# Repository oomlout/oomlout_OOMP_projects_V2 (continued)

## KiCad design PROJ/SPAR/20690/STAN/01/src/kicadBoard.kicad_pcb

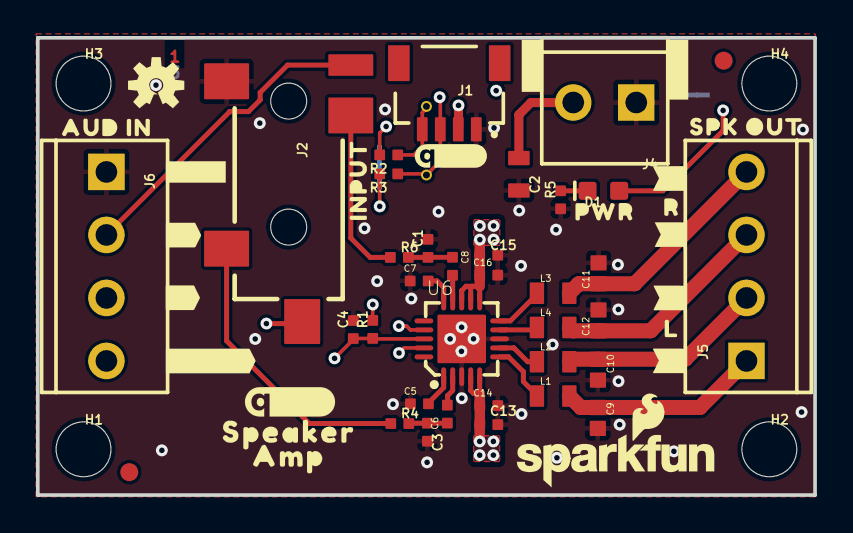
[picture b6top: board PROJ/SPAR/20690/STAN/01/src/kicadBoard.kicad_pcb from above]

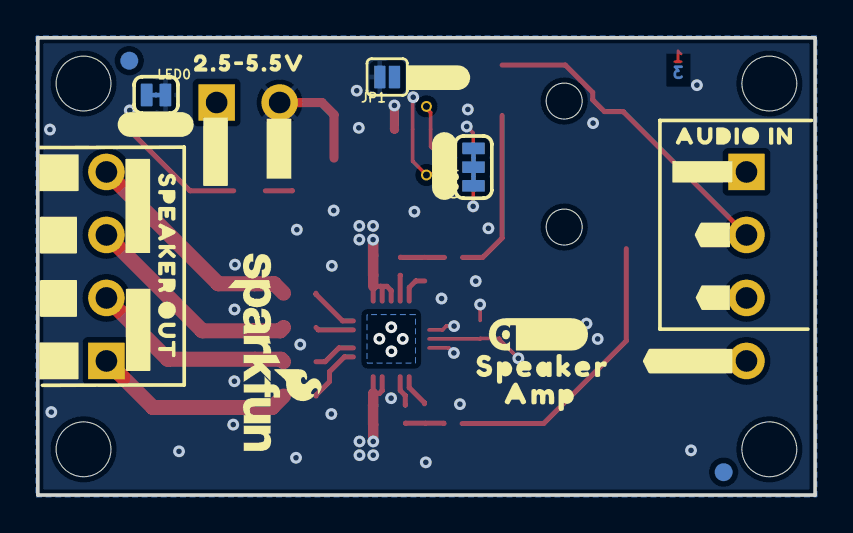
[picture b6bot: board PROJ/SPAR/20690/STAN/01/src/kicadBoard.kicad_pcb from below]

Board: 4 copper layers, 43.2 x 25.4 mm, 92 parts (27 on the bottom side), 28 nets.

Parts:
C1, C3: 47nF; 0402-TIGHT
C2: 10uF; 0805
C4, C14, C16: 0.1uF; 0402-TIGHT
C5, C6, C7, C8, C13, C15: 1.0uF; 0402-TIGHT
C9, C10, C11, C12: 1nF; 0402
D1: RED; LED-0603
FD1, FD2, FD3, FD4: FIDUCIAL1X2; FIDUCIAL-1X2
FRAME2: FRAME-LETTER; CREATIVE_COMMONS
H1, H2, H3, H4: STAND-OFFTIGHT; STAND-OFF-TIGHT
I2C0: JUMPER-SMT_3_2-NC_TRACE_SILK; SMT-JUMPER_3_2-NC_TRACE_SILK
J1: QWIIC; JST04_1MM_RA
J2: TRS_INPUT; AUDIO-JACK-3.5MM-SMD
J4: SCREWTERMINAL-3.5MM-2
J5: SCREWTERMINAL-3.5MM-4
J6: SCREW; SCREWTERMINAL-3.5MM-4
JP1: JP1; SMT-JUMPER_2_NO_SILK
L1, L2, L3, L4: 220Ω; 0805
LED0: SMT-JUMPER_2_NC_TRACE_SILK
LOGO1: QWIIC_LOGO_4MM; QWIIC_5MM
LOGO2: SFE_LOGO_NAME_FLAME.1_INCH; SFE_LOGO_NAME_FLAME_.1
LOGO3: QWIIC_LOGO_4MM; QWIIC_4MM
LOGO4: OSHW-LOGOS; OSHW-LOGO-S
LOGO6: SPECIAL_INSTRUCTIONS-ORDERING; ORDERING_INSTRUCTIONS
R1: 100k; 0402-TIGHT
R2, R3: 2.2k; 0402-TIGHT
R4, R6: 100; 0402-TIGHT
R5: 1k; 0402-TIGHT
TP1, TP2: TP_15TH
U6: TPA2016D2; QFN-20-0.5MM
U$1, U$4: SPEAKER0
U$2: #I2C#0
U$3: INPUT0
U$5: PWR26
U$6, U$8: AMP0
U$7: QWIIC_5.5MM
U$9, U$12: ###15
U$10, U$11: ###16
U$13: ##SHDN##3
U$14: R21
U$15: #VIN#24
U$16: L5
U$17: #R#11
U$18: #L#33
U$19: #L#12
U$20, U$25, U$29: #GND#25
U$21: SPK_OUT22
U$22: AUD_IN23
U$23: 2#5#5#5V24
U$24: #LED#27
U$26: #VIN#30
U$27: #GND#31
U$28: #R#34
U$30: SFE_LOGO_NAME_FLAME_.1
U$31, U$32: ###40
U$33: SPEAKER_OUT37
U$34: AUDIO_IN39
U$35, U$36: ###41
U$37: #LEFT#43
U$38: #RIGHT#44
U$39: #JP1#2
U$40: ##SHDN##2

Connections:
3.3V: I2C0.2, J1.2, JP1.1
GND: C1.2, C2.2, C3.2, C4.2, C5.1, C7.1, C9.2, C10.2, C11.2, C12.2, C13.2, C14.2, C15.2, C16.2, J1.1, J2.SLEEVE, J4.1, J6.1, R5.1, U6.3, U6.8, U6.PAD
INL: J2.TIP, R4.1
INL_SCRWPN: J2.TSH, J6.3
INR: J2.RING, R6.1
INR_SCRWPN: J2.RSH, J6.2
unnamed: L1.1, U6.6
unnamed: L2.1, U6.7
unnamed: C1.1, C8.1, R6.2
unnamed: D1.C, R5.2
unnamed: C3.1, C6.1, R4.2
unnamed: D1.A, LED0.1
unnamed: I2C0.3, R2.2
unnamed: I2C0.1, R3.2
unnamed: L3.1, U6.10
unnamed: L4.1, U6.9
unnamed: C8.2, U6.14
unnamed: C5.2, U6.1
unnamed: C6.2, U6.2
unnamed: C7.2, U6.15
SCL: J1.4, R2.1, TP1.1, U6.17
SDA: J1.3, R3.1, TP2.1, U6.19
SPK_L_+: C9.1, J5.1, L1.2
SPK_L_-: C10.1, J5.2, L2.2
SPK_R_+: C11.1, J5.4, L3.2
SPK_R_-: C12.1, J5.3, L4.2
VCC: C2.1, C13.1, C14.1, C15.1, C16.1, J4.2, JP1.2, LED0.2, R1.2, U6.4, U6.5, U6.11, U6.12, U6.13
~SDZ: C4.1, J6.4, R1.1, U6.18

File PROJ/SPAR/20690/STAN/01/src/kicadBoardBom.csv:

"Id";"Designator";"Package";"Quantity";"Designation";"Supplier and ref";
1;"C14,C16,C4";"0402-TIGHT";3;"0.1uF";;;
2;"U$9,U$12";"###15";2;"";;;
3;"R2,R3";"0402-TIGHT";2;"2.2k";;;
4;"FRAME2";"CREATIVE_COMMONS";1;"FRAME-LETTER";;;
5;"J6";"SCREWTERMINAL-3.5MM-4";1;"SCREW";;;
6;"J4";"SCREWTERMINAL-3.5MM-2";1;"";;;
7;"J5";"SCREWTERMINAL-3.5MM-4";1;"";;;
8;"U$11,U$10";"###16";2;"";;;
9;"C11,C10,C9,C12";"0402";4;"1nF";;;
10;"H3,H4,H1,H2";"STAND-OFF-TIGHT";4;"STAND-OFFTIGHT";;;
11;"U$17";"#R#11";1;"";;;
12;"U$22";"AUD_IN23";1;"";;;
13;"R6,R4";"0402-TIGHT";2;"100";;;
14;"U6";"QFN-20-0.5MM";1;"TPA2016D2";;;
15;"FD3,FD1,FD2,FD4";"FIDUCIAL-1X2";4;"FIDUCIAL1X2";;;
16;"U$19";"#L#12";1;"";;;
17;"C3,C1";"0402-TIGHT";2;"47nF";;;
18;"U$20,U$25,U$29";"#GND#25";3;"";;;
19;"C2";"0805";1;"10uF";;;
20;"U$3";"INPUT0";1;"";;;
21;"C5,C6,C8,C13,C15,C7";"0402-TIGHT";6;"1.0uF";;;
22;"D1";"LED-0603";1;"RED";;;
23;"LOGO6";"ORDERING_INSTRUCTIONS";1;"SPECIAL_INSTRUCTIONS-ORDERING";;;
24;"TP2,TP1";"TP_15TH";2;"";;;
25;"U$1,U$4";"SPEAKER0";2;"";;;
26;"R1";"0402-TIGHT";1;"100k";;;
27;"J2";"AUDIO-JACK-3.5MM-SMD";1;"TRS_INPUT";;;
28;"U$16";"L5";1;"";;;
29;"U$14";"R21";1;"";;;
30;"U$21";"SPK_OUT22";1;"";;;
31;"L1,L2,L4,L3";"0805";4;"220Ω";;;
32;"U$15";"#VIN#24";1;"";;;
33;"U$30";"SFE_LOGO_NAME_FLAME_.1";1;"";;;
34;"LOGO4";"OSHW-LOGO-S";1;"OSHW-LOGOS";;;
35;"LOGO3";"QWIIC_4MM";1;"QWIIC_LOGO_4MM";;;
36;"J1";"JST04_1MM_RA";1;"QWIIC";;;
37;"LOGO1";"QWIIC_5MM";1;"QWIIC_LOGO_4MM";;;
38;"U$40";"##SHDN##2";1;"";;;
39;"U$5";"PWR26";1;"";;;
40;"U$6,U$8";"AMP0";2;"";;;
41;"R5";"0402-TIGHT";1;"1k";;;
42;"U$2";"#I2C#0";1;"";;;
43;"LED0";"SMT-JUMPER_2_NC_TRACE_SILK";1;"";;;
44;"U$33";"SPEAKER_OUT37";1;"";;;
45;"U$13";"##SHDN##3";1;"";;;
46;"U$39";"#JP1#2";1;"";;;
47;"U$31,U$32";"###40";2;"";;;
48;"U$36,U$35";"###41";2;"";;;
49;"U$7";"QWIIC_5.5MM";1;"";;;
50;"U$34";"AUDIO_IN39";1;"";;;
51;"I2C0";"SMT-JUMPER_3_2-NC_TRACE_SILK";1;"JUMPER-SMT_3_2-NC_TRACE_SILK";;;
52;"U$26";"#VIN#30";1;"";;;
53;"U$24";"#LED#27";1;"";;;
54;"U$28";"#R#34";1;"";;;
55;"JP1";"SMT-JUMPER_2_NO_SILK";1;"JP1";;;
56;"U$23";"2#5#5#5V24";1;"";;;
57;"U$37";"#LEFT#43";1;"";;;
58;"U$18";"#L#33";1;"";;;
59;"LOGO2";"SFE_LOGO_NAME_FLAME_.1";1;"SFE_LOGO_NAME_FLAME.1_INCH";;;
60;"U$38";"#RIGHT#44";1;"";;;
61;"U$27";"#GND#31";1;"";;;

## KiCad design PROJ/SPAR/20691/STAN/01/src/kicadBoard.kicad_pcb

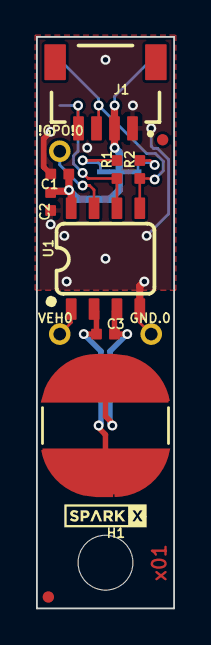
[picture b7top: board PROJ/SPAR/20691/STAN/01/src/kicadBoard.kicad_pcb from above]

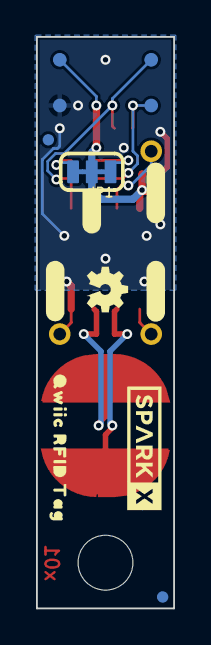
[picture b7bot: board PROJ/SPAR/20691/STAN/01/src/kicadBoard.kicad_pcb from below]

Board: 2 copper layers, 7.6 x 31.8 mm, 31 parts (14 on the bottom side), 10 nets.

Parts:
!GPO!0: 1X01_1MM_NO_SILK
ANT0: 4.7μH; W3102
C1: 0.1uF; 0402-TIGHT
C2: 2.2uF; 0402-TIGHT
C3: 0.5pF; 0402-TIGHT
FD1, FD2, FD3, FD4: FIDUCIALUFIDUCIAL; FIDUCIAL-MICRO
FRAME2: FRAME-LETTER; CREATIVE_COMMONS
GND0: TEST-POINT3; PAD.03X.03
GND.0: 1X01_1MM_NO_SILK
H1: STAND-OFFTIGHT; STAND-OFF-TIGHT
J1: QWIIC_RIGHT_ANGLE; JST04_1MM_RA
JP1: JUMPER-SMT_3_2-NC_TRACE_SILK; SMT-JUMPER_3_2-NC_TRACE_SILK
LOGO1: SPECIAL_INSTRUCTIONS-ORDERING; ORDERING_INSTRUCTIONS
LOGO2: OSHW-LOGOMINI; OSHW-LOGO-MINI
R1, R2: 2.2k; 0402-TIGHT
SCL0: TEST-POINT3; PAD.03X.03
SDA0: TEST-POINT3; PAD.03X.03
U1: ST25DV64KC; SO08
U$1: SPARKX-LOGO2; SPARKX-TINY
U$2: ##GPO##0
U$3: QWIIC_RFID_TAG0
U$4: #VEH#0
U$5: #I�C#0
U$6: #GND#0
U$20: SPARKX-LOGO3; SPARKX-SMALL
UNK3V3: TEST-POINT3; PAD.03X.03
VEH0: 1X01_1MM_NO_SILK

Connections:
3.3V: C1.1, C2.1, J1.2, JP1.2, U1.8, UNK3V3.1
GND: C1.2, C2.2, GND0.1, GND.0.1, J1.1, U1.4
unnamed: ANT0.2, C3.2, U1.3
unnamed: ANT0.1, C3.1, U1.2
unnamed: JP1.3, R2.2
unnamed: JP1.1, R1.2
SCL: J1.4, R1.1, SCL0.1, U1.6
SDA: J1.3, R2.1, SDA0.1, U1.5
VEH: U1.1, VEH0.1
~GPO: !GPO!0.1, U1.7

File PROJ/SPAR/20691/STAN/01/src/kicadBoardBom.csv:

"Id";"Designator";"Package";"Quantity";"Designation";"Supplier and ref";
1;"FD3,FD1,FD4,FD2";"FIDUCIAL-MICRO";4;"FIDUCIALUFIDUCIAL";;;
2;"FRAME2";"CREATIVE_COMMONS";1;"FRAME-LETTER";;;
3;"LOGO1";"ORDERING_INSTRUCTIONS";1;"SPECIAL_INSTRUCTIONS-ORDERING";;;
4;"!GPO!0,GND.0,VEH0";"1X01_1MM_NO_SILK";3;"";;;
5;"H1";"STAND-OFF-TIGHT";1;"STAND-OFFTIGHT";;;
6;"U1";"SO08";1;"ST25DV64KC";;;
7;"U$1";"SPARKX-TINY";1;"SPARKX-LOGO2";;;
8;"J1";"JST04_1MM_RA";1;"QWIIC_RIGHT_ANGLE";;;
9;"C1";"0402-TIGHT";1;"0.1uF";;;
10;"C2";"0402-TIGHT";1;"2.2uF";;;
11;"C3";"0402-TIGHT";1;"0.5pF";;;
12;"R2,R1";"0402-TIGHT";2;"2.2k";;;
13;"ANT0";"W3102";1;"4.7μH";;;
14;"GND0,SDA0,UNK3V3,SCL0";"PAD.03X.03";4;"TEST-POINT3";;;
15;"JP1";"SMT-JUMPER_3_2-NC_TRACE_SILK";1;"JUMPER-SMT_3_2-NC_TRACE_SILK";;;
16;"U$5";"#I�C#0";1;"";;;
17;"U$3";"QWIIC_RFID_TAG0";1;"";;;
18;"LOGO2";"OSHW-LOGO-MINI";1;"OSHW-LOGOMINI";;;
19;"U$6";"#GND#0";1;"";;;
20;"U$2";"##GPO##0";1;"";;;
21;"U$4";"#VEH#0";1;"";;;
22;"U$20";"SPARKX-SMALL";1;"SPARKX-LOGO3";;;

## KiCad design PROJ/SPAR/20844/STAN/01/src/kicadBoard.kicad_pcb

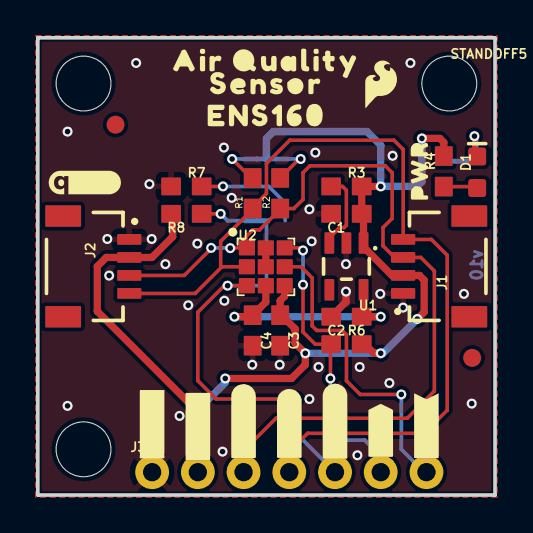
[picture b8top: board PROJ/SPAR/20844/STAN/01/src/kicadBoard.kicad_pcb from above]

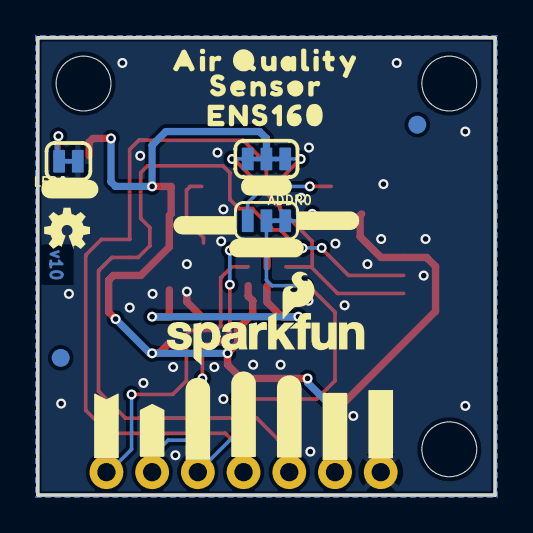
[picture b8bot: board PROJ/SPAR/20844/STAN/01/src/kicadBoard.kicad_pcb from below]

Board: 2 copper layers, 25.4 x 25.4 mm, 58 parts (22 on the bottom side), 15 nets.

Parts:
ADDR0: JUMPER-SMT_3_1-NC_TRACE_SILK; SMT-JUMPER_3_1-NC_TRACE_SILK
C1, C2: 1.0uF; 0603
C3: 0.1uF; 0603
C4: 10uF; 0603
D1: RED; LED-0603
FD1, FD2, FD3, FD4: FIDUCIAL1X2; FIDUCIAL-1X2
FRAME1: FRAME-LETTER; CREATIVE_COMMONS
I2C_PU0: S_MODE; SMT-JUMPER_3_2-NC_TRACE_SILK
J1, J2: QWIIC_RIGHT_ANGLE; JST04_1MM_RA
J3: 1X07_NO_SILK
LED0: JUMPER-SMT_2_NC_TRACE_SILK; SMT-JUMPER_2_NC_TRACE_SILK
LOGO2: OSHW-LOGOMINI; OSHW-LOGO-MINI
LOGO3: SFE_LOGO_NAME_FLAME.1_INCH; SFE_LOGO_NAME_FLAME_.1
LOGO4: QWIIC_LOGO_4MM; QWIIC_4MM
R1, R2: 2.2k; 0603
R3, R6, R7, R8: 10k; 0603
R4: 1k; 0603
STANDOFF1, STANDOFF2, STANDOFF5: STAND-OFFTIGHT; STAND-OFF-TIGHT
U1: AP2127K-1.8V; SOT23-5
U2: ENS-160; LGA-9
U$1, U$9: #GND#3
U$2, U$10: #3V3#4
U$3: #SDA#5
U$4: #SCL#4
U$5, U$28: ENS16016
U$6: #ADDR#6
U$7: #SCLK#16021
U$8: #ADR#441018
U$11: ##INT##9
U$12, U$17: AIR_QUALITY441014
U$13, U$19: SENSOR441015
U$14: #0X53#16019
U$15: #0X52#16019
U$16: #LED#11
U$18: ##INT##6
U$20: SFE_LOGO_FLAME_.1
U$21: PWR9
U$22: ##CS##16019
U$23: #POCI#16020
U$24: #PICO#16021
U$25: #I2C#11
U$27: ##CS##441016

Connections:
1.8V: C2.1, C4.1, U1.5, U2.P4
3.3V: C1.1, C3.1, I2C_PU0.2, J1.2, J2.2, J3.2, R3.2, R4.2, R6.2, R8.2, U1.1, U2.P5
GND: C1.2, C2.2, C3.2, C4.2, J1.1, J2.1, J3.1, LED0.1, R7.1, U1.2, U2.P8, U2.P9
unnamed: R3.1, U1.3
unnamed: D1.A, R4.1
unnamed: D1.C, LED0.2
unnamed: ADDR0.3, R8.1
unnamed: I2C_PU0.1, R1.2
unnamed: I2C_PU0.3, R2.2
unnamed: ADDR0.1, R7.2
PICO/SDA: J1.3, J2.3, J3.3, R2.1, U2.P1
POCI/ADDR: ADDR0.2, J3.5, U2.P3
SCLK/SCL: J1.4, J2.4, J3.4, R1.1, U2.P2
~CS: J3.6, R6.1, U2.P7
~INT: J3.7, U2.P6

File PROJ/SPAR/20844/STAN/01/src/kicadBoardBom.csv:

"Id";"Designator";"Package";"Quantity";"Designation";"Supplier and ref";
1;"C3";"0603";1;"0.1uF";;;
2;"U$17,U$12";"AIR_QUALITY441014";2;"";;;
3;"U$3";"#SDA#5";1;"";;;
4;"U$19,U$13";"SENSOR441015";2;"";;;
5;"J2,J1";"JST04_1MM_RA";2;"QWIIC_RIGHT_ANGLE";;;
6;"FD4,FD3,FD2,FD1";"FIDUCIAL-1X2";4;"FIDUCIAL1X2";;;
7;"C1,C2";"0603";2;"1.0uF";;;
8;"U$2,U$10";"#3V3#4";2;"";;;
9;"U$8";"#ADR#441018";1;"";;;
10;"R1,R2";"0603";2;"2.2k";;;
11;"R8,R7,R6,R3";"0603";4;"10k";;;
12;"U$21";"PWR9";1;"";;;
13;"U$18";"##INT##6";1;"";;;
14;"STANDOFF5,STANDOFF1,STANDOFF2";"STAND-OFF-TIGHT";3;"STAND-OFFTIGHT";;;
15;"U$20";"SFE_LOGO_FLAME_.1";1;"";;;
16;"FRAME1";"CREATIVE_COMMONS";1;"FRAME-LETTER";;;
17;"J3";"1X07_NO_SILK";1;"";;;
18;"U1";"SOT23-5";1;"AP2127K-1.8V";;;
19;"U$1,U$9";"#GND#3";2;"";;;
20;"R4";"0603";1;"1k";;;
21;"U2";"LGA-9";1;"ENS-160";;;
22;"U$28,U$5";"ENS16016";2;"";;;
23;"LOGO4";"QWIIC_4MM";1;"QWIIC_LOGO_4MM";;;
24;"U$4";"#SCL#4";1;"";;;
25;"D1";"LED-0603";1;"RED";;;
26;"C4";"0603";1;"10uF";;;
27;"U$27";"##CS##441016";1;"";;;
28;"LOGO2";"OSHW-LOGO-MINI";1;"OSHW-LOGOMINI";;;
29;"U$15";"#0X52#16019";1;"";;;
30;"I2C_PU0";"SMT-JUMPER_3_2-NC_TRACE_SILK";1;"S_MODE";;;
31;"U$24";"#PICO#16021";1;"";;;
32;"U$16";"#LED#11";1;"";;;
33;"U$23";"#POCI#16020";1;"";;;
34;"U$14";"#0X53#16019";1;"";;;
35;"ADDR0";"SMT-JUMPER_3_1-NC_TRACE_SILK";1;"JUMPER-SMT_3_1-NC_TRACE_SILK";;;
36;"LED0";"SMT-JUMPER_2_NC_TRACE_SILK";1;"JUMPER-SMT_2_NC_TRACE_SILK";;;
37;"U$7";"#SCLK#16021";1;"";;;
38;"U$22";"##CS##16019";1;"";;;
39;"LOGO3";"SFE_LOGO_NAME_FLAME_.1";1;"SFE_LOGO_NAME_FLAME.1_INCH";;;
40;"U$25";"#I2C#11";1;"";;;
41;"U$11";"##INT##9";1;"";;;
42;"U$6";"#ADDR#6";1;"";;;
